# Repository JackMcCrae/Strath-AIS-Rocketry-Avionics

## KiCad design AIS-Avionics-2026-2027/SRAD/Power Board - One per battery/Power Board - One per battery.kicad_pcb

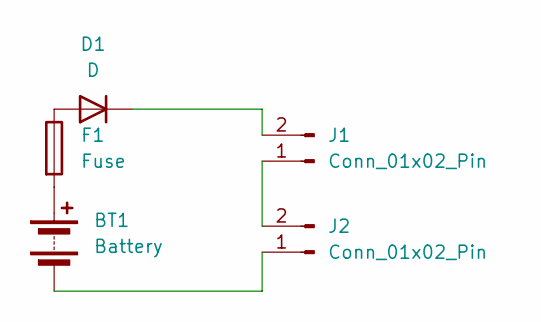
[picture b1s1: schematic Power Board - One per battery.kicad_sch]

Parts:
BT1: Battery; AIS Battery Holder V1
D1: D; TO-264-2_Vertical
F1: Fuse; Fuseholder_Littelfuse_445_030_series_5x30mm
J1, J2: Conn_01x02_Pin; JST_PH_B2B-PH-K_1x02_P2.00mm_Vertical

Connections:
unnamed: BT1.1 (+), F1.2
unnamed: BT1.2 (-), J2.1
unnamed: D1.2 (A), F1.1
unnamed: D1.1 (K), J1.2
unnamed: J1.1, J2.2

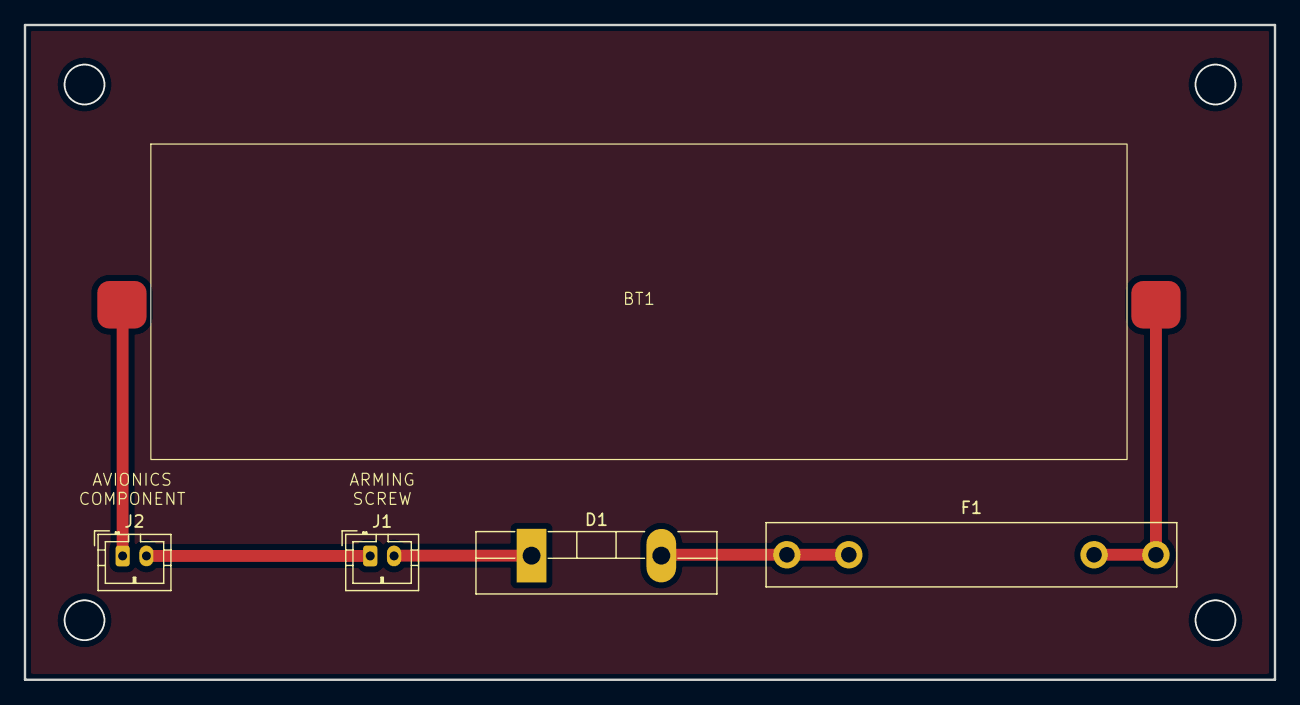
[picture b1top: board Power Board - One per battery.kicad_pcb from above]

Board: 2 copper layers, 105.0 x 55.0 mm, 5 parts (0 on the bottom side), 5 nets.

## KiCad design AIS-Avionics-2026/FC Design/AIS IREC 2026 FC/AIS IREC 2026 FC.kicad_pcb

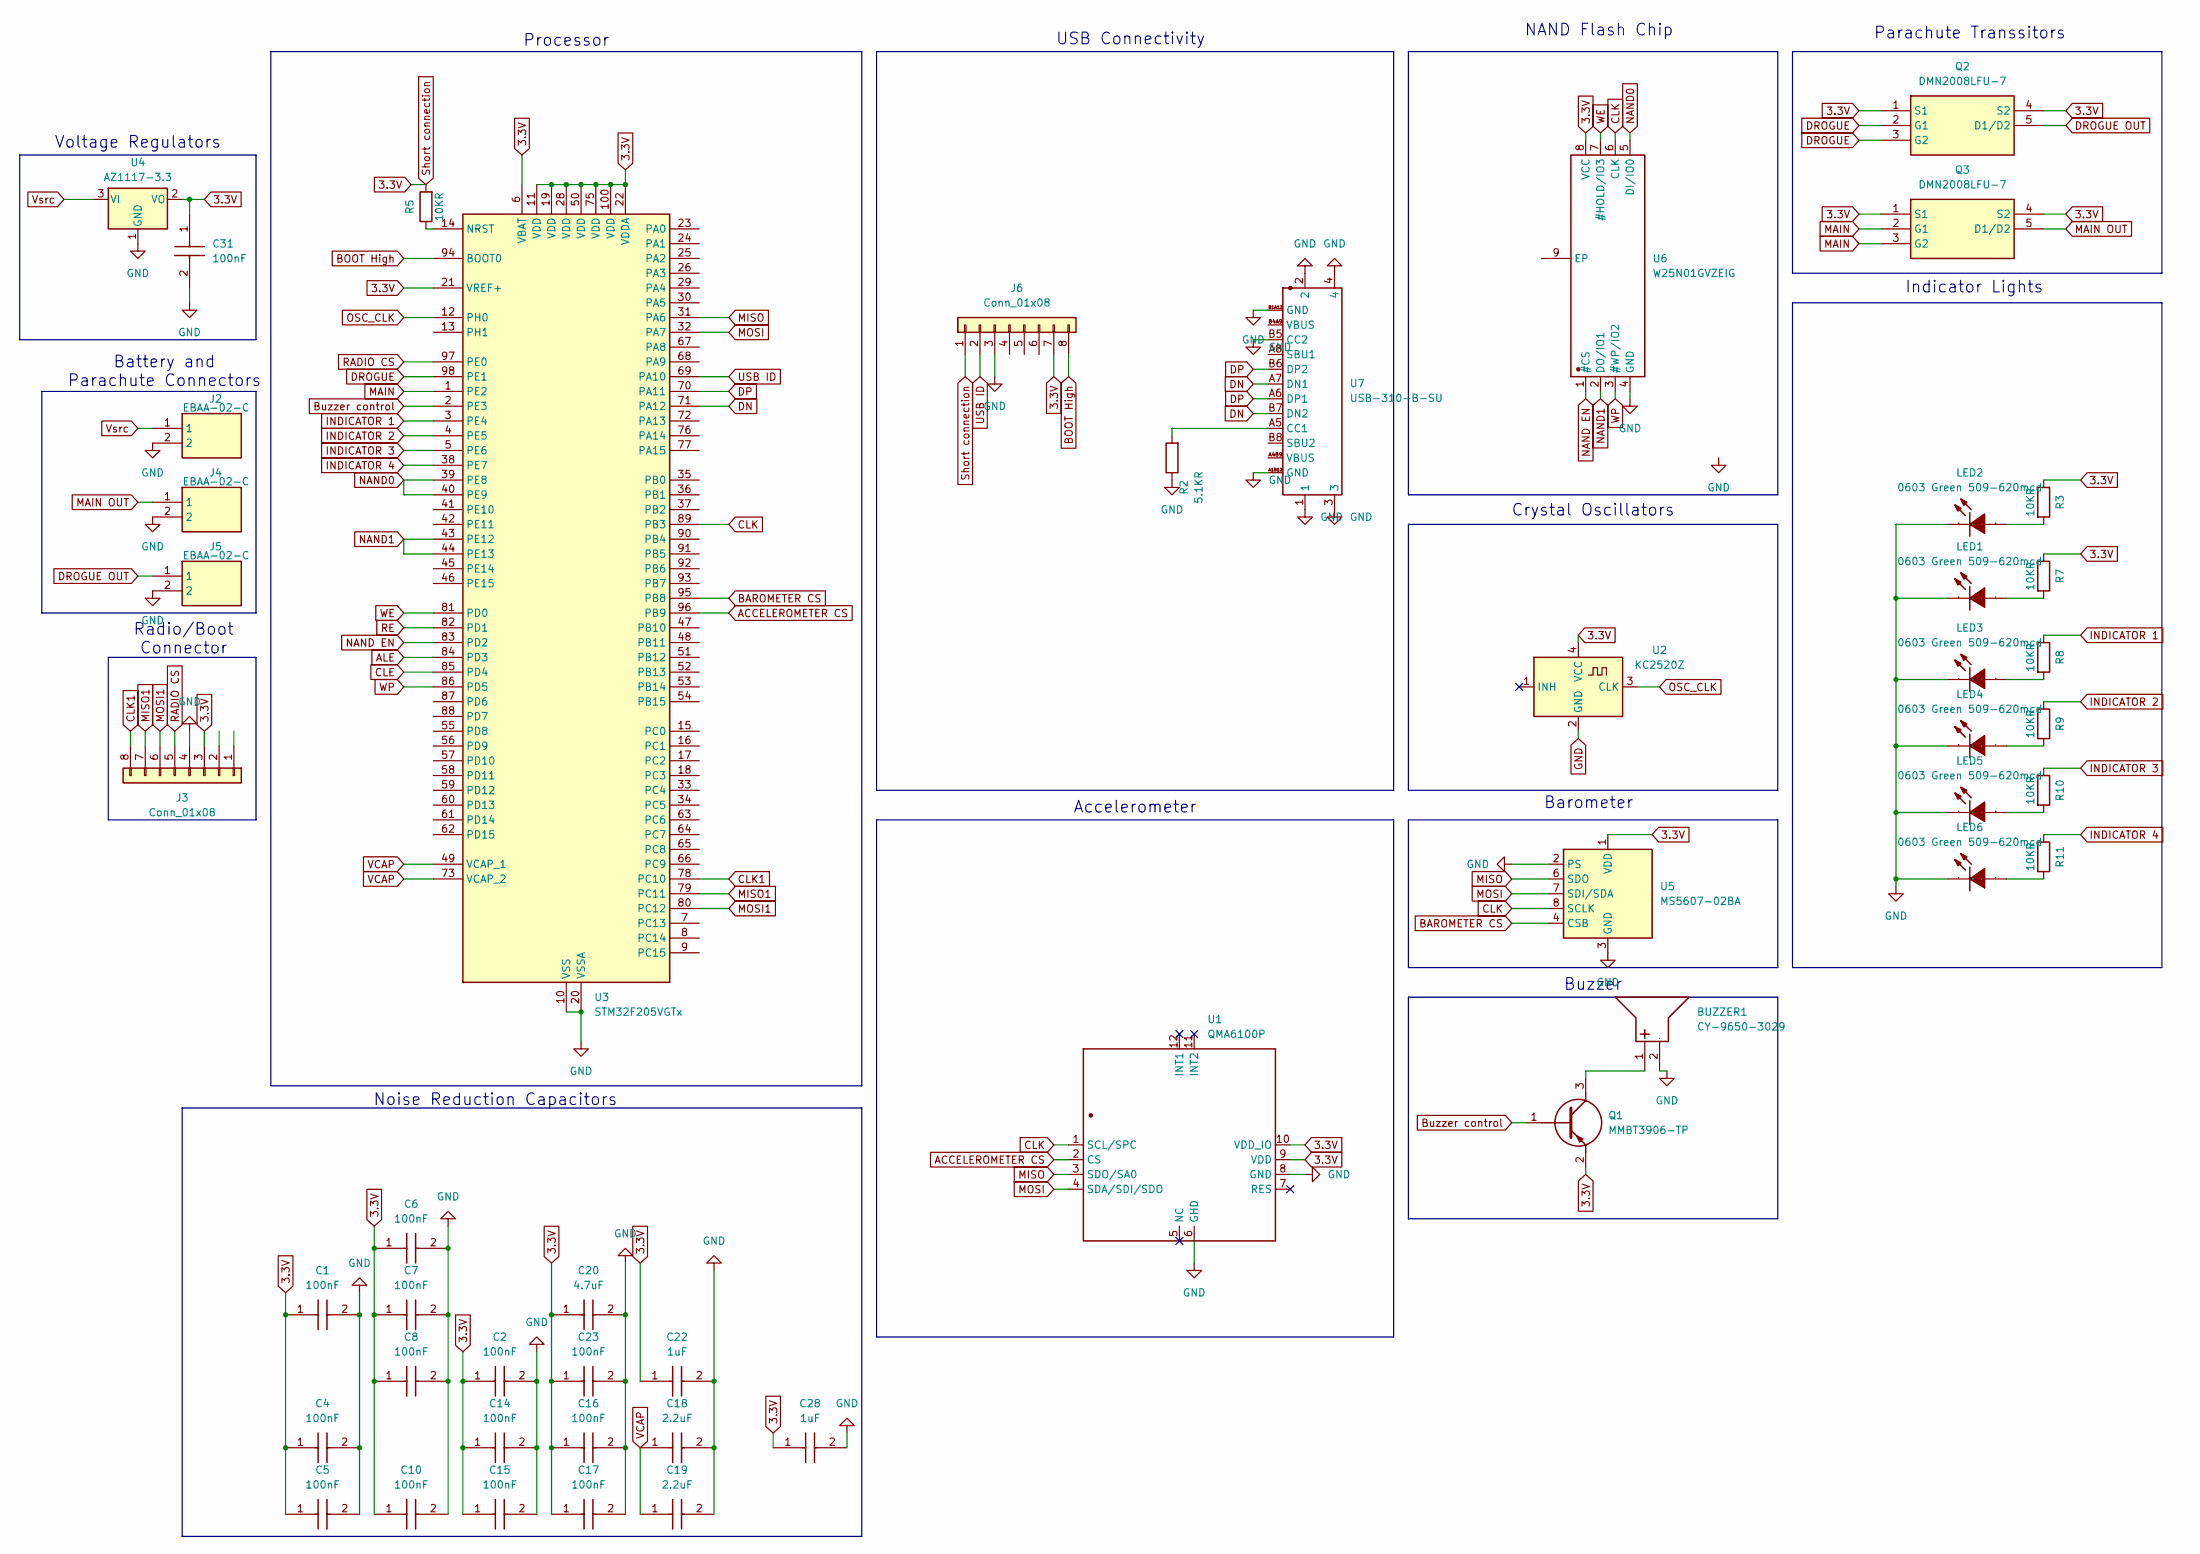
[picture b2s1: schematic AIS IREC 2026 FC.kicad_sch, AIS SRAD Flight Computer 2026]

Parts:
BUZZER1: CY-9650-3029; MLT-9650; Manufacturer Part Cy-9650-3029
C1, C2, C4, C5, C6, C7, C8, C10, C14, C15, C16, C17, C23, C31: 100nF; GRM022C81C222KE01L; Mouser Part Number 81-GRM022R61A104KE1L
C18, C19: 2.2uF; GRM033D70J224ME01D; Mouser Part Number 81-GRM033R61A225KE7D
C20: 4.7uF; GRM033D70J224ME01D; Mouser Part Number 81-GRM035R60J475ME5D
C22, C28: 1uF; CAPC0603X33N; Mouser Part Number 81-GRT033R60J105ME3D
J2, J4, J5: EBAA-02-C; EBAA02C; Mouser Part Number 737-EBAA-02-C
J3, J6: Conn_01x08; Hirose_DF13-08P-1.25DSA_1x08_P1.25mm_Vertical
LED1, LED2, LED3, LED4, LED5, LED6: 0603 Green 509-620mcd; LED0603-RD; Manufacturer Part KT-0603G
Q1: MMBT3906-TP; SOT95P237X125-3N; Mouser Part Number 833-MMBT3906-TP
Q2, Q3: DMN2008LFU-7; DMN2008LFU7; Mouser Part Number 621-DMN2008LFU-7
R2: 5.1KR; R_0201_0603Metric
R3, R5, R7, R8, R9, R10, R11: 10KR; R_0201_0603Metric
U1: QMA6100P; MR ACCELEROMETER; Manufacturer Part QMA6100P
U2: KC2520Z; Oscillator_SMD_Kyocera_KC2520Z-4Pin_2.5x2.0mm
U3: STM32F205VGTx; LQFP-100_14x14mm_P0.5mm
U4: AZ1117-3.3; SOT-223-3_TabPin2
U5: MS5607-02BA; LGA-8_3x5mm_P1.25mm
U6: W25N01GVZEIG; NAND FLASH; Manufacturer Part W25N01GVZEIG
U7: USB-310-B-SU; USB 310F B; Manufacturer Part USB-310-B-SU

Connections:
3.3V: C1.1, C2.1, C4.1, C5.1, C6.1, C7.1, C8.1, C10.1, C14.1, C15.1, C16.1, C17.1, C20.1, C22.1, C23.1, C28.1, C31.1, J3.3, J6.1, J6.7, Q1.2 (E), Q2.1 (S1), Q2.4 (S2), Q3.1 (S1), Q3.4 (S2), R3.1, R5.2, R7.1, U1.9 (VDD), U1.10 (VDD_IO), U2.4 (VCC), U3.6 (VBAT), U3.11 (VDD), U3.19 (VDD), U3.21 (VREF+), U3.22 (VDDA), U3.28 (VDD), U3.50 (VDD), U3.75 (VDD), U3.100 (VDD), U4.2 (VO), U5.1 (VDD), U6.8 (VCC)
ACCELEROMETER CS: U1.2 (CS), U3.96 (PB9)
ALE: U3.84 (PD3)
BAROMETER CS: U3.95 (PB8), U5.4 (CSB), U5.5 (CSB)
BOOT High: J6.8, U3.94 (BOOT0)
Buzzer control: Q1.1 (B), U3.2 (PE3)
CLE: U3.85 (PD4)
CLK: U1.1 (SCL/SPC), U3.89 (PB3), U5.8 (SCLK), U6.6 (CLK)
CLK1: J3.8, U3.78 (PC10)
DN: U3.71 (PA12), U7.A7 (DN1), U7.B7 (DN2)
DP: U3.70 (PA11), U7.A6 (DP1), U7.B6 (DP2)
DROGUE: Q2.2 (G1), Q2.3 (G2), U3.98 (PE1)
DROGUE OUT: J5.1, Q2.5 (D1/D2)
GND: BUZZER1.2 (-), C1.2, C2.2, C4.2, C5.2, C6.2, C7.2, C8.2, C10.2, C14.2, C15.2, C16.2, C17.2, C18.2, C19.2, C20.2, C22.2, C23.2, C28.2, C31.2, J2.2, J3.4, J4.2, J5.2, J6.3, LED1.1 (K), LED2.1 (K), LED3.1 (K), LED4.1 (K), LED5.1 (K), LED6.1 (K), R2.1, U1.6 (GHD), U1.8 (GND), U2.2 (GND), U3.10 (VSS), U3.20 (VSSA), U3.27 (VSS), U3.74 (VSS), U4.1 (GND), U5.2 (PS), U5.3 (GND), U6.4 (GND), U7.1, U7.2, U7.3, U7.4, U7.A1B12 (GND), U7.B1A12 (GND), U7.B5 (CC2)
INDICATOR 1: R8.1, U3.3 (PE4)
INDICATOR 2: R9.1, U3.4 (PE5)
INDICATOR 3: R10.1, U3.5 (PE6)
INDICATOR 4: R11.1, U3.38 (PE7)
MAIN: Q3.2 (G1), Q3.3 (G2), U3.1 (PE2)
MAIN OUT: J4.1, Q3.5 (D1/D2)
MISO: U1.3 (SDO/SA0), U3.31 (PA6), U5.6 (SDO)
MISO1: J3.7, U3.79 (PC11)
MOSI: U1.4 (SDA/SDI/SDO), U3.32 (PA7), U5.7 (SDI/SDA)
MOSI1: J3.6, U3.80 (PC12)
NAND0: U3.39 (PE8), U3.40 (PE9), U6.5 (DI/IO0)
NAND1: U3.43 (PE12), U3.44 (PE13), U6.2 (DO/IO1)
NAND EN: U3.83 (PD2), U6.1 (#CS)
unnamed: BUZZER1.1 (+), Q1.3 (C)
unnamed: LED1.2 (A), R7.2
unnamed: LED2.2 (A), R3.2
unnamed: LED3.2 (A), R8.2
unnamed: LED4.2 (A), R9.2
unnamed: LED5.2 (A), R10.2
unnamed: LED6.2 (A), R11.2
unnamed: R5.1, U3.14 (NRST)
unnamed: R2.2, U7.A5 (CC1)
OSC_CLK: U2.3 (CLK), U3.12 (PH0)
RADIO CS: J3.5, U3.97 (PE0)
RE: U3.82 (PD1)
USB ID: J6.2, U3.69 (PA10)
VCAP: C18.1, C19.1, U3.49 (VCAP_1), U3.73 (VCAP_2)
Vsrc: J2.1, U4.3 (VI)
WE: U3.81 (PD0), U6.7 (#HOLD/IO3)
WP: U3.86 (PD5), U6.3 (#WP/IO2)

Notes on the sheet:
Processor
Indicator Lights
Voltage Regulators
USB Connectivity
Battery and Parachute Connectors
Crystal Oscillators
Barometer
Noise Reduction Capacitors
Radio/Boot Connector
NAND Flash Chip
Buzzer
Accelerometer
Parachute Transsitors

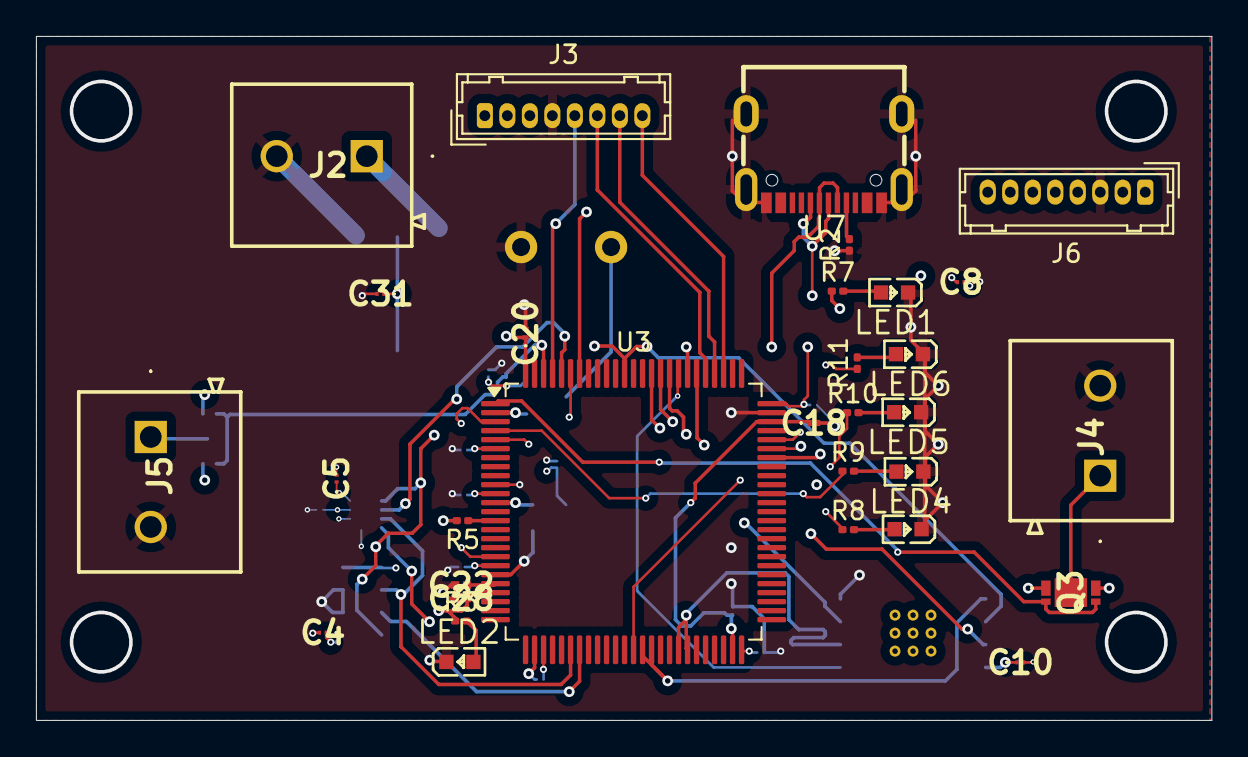
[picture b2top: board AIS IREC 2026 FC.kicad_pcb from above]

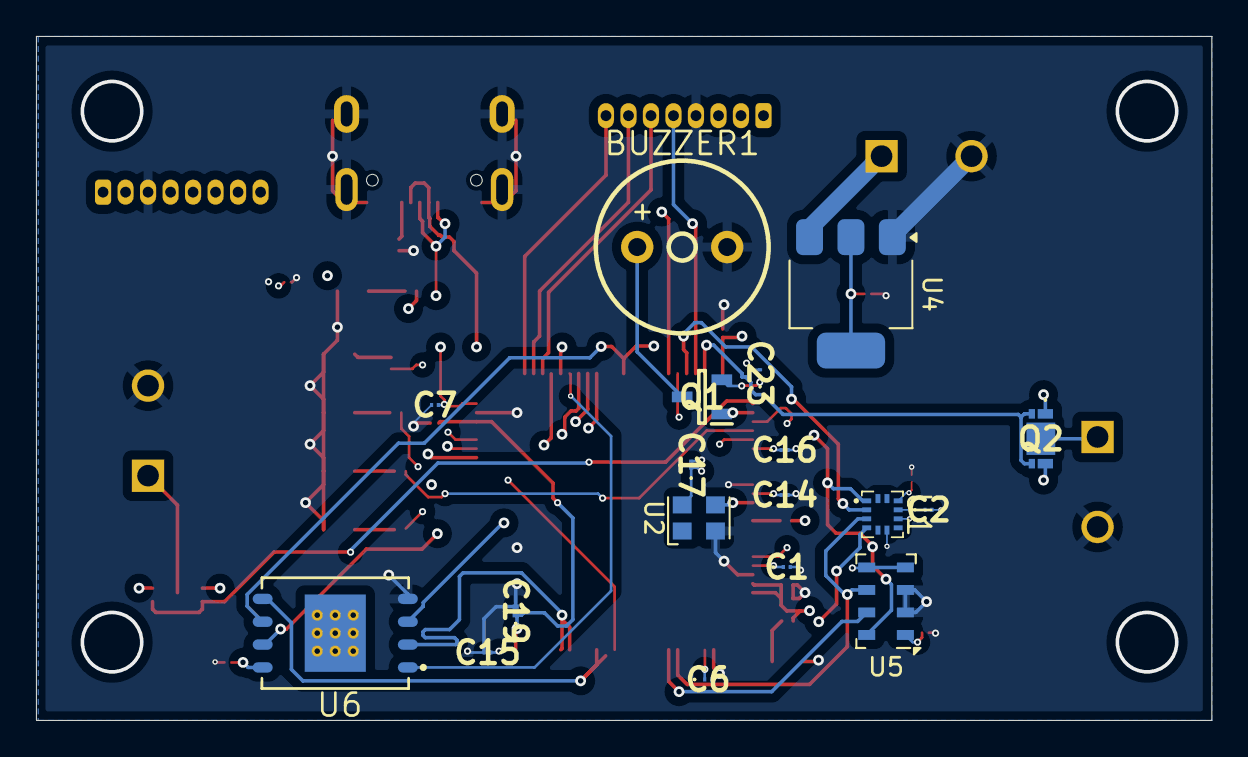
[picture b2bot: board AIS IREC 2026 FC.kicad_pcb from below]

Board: 4 copper layers, 65.3 x 38.0 mm, 49 parts (18 on the bottom side), 41 nets.

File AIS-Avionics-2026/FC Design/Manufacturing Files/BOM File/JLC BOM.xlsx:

Component | Designator | Footprint
CY-9650 | BUZZER1 | MLT-9650
100nF | C1,C2,C4,C5,C6,C7,C8,C10,C14,C15,C16,C17,C23,C31 | GRM022C81C222KE01L
2.2uF | C18,C19 | GRM033D70J224ME01D
4.7uF | C20 | GRM033D70J224ME01D
1uF | C22,C28 | CAPC0603X33N
0603 Green 509-620mcd | LED1,LED2,LED3,LED4,LED5,LED6 | LED0603-RD
10KR | R9,R5,R3,R8,R7,R10,R11 | R_0201_0603Metric
5.1KR | R2 | R_0201_0603Metric
DMN2008LFU-7 | Q3,Q2 | DMN2008LFU7
Conn_01x08 | J6,J3 | Hirose_DF13-08P-1.25DSA_1x08_P1.25mm_Vertical
EBAA-02-C | J5,J4,J2 | EBAA02C
USB-310-B-SU | U7 | UBS-310-B-SU
STM32F205VGT | U3 | STM32F205VGT
MMBT3906-TP | Q1 | SOT95P237X125-3N
KC2520Z | U2 | Oscillator_SMD_Kyocera_KC2520Z-4Pin_2.5x2.0mm
AZ1117-3.3 | U4 | SOT-223-3_TabPin2
MS5607-02BA | U5 | LGA-8_3x5mm_P1.25mm
QMA6100P | U1 | QMA6100P
W25N01GVZEIG | U6 | W25N01GVZEIG

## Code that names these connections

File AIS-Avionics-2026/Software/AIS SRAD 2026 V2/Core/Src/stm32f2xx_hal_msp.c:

/* USER CODE BEGIN Header */
/**
  ******************************************************************************
  * @file         stm32f2xx_hal_msp.c
  * @brief        This file provides code for the MSP Initialization
  *               and de-Initialization codes.
  ******************************************************************************
  * @attention
  *
  * Copyright (c) 2026 STMicroelectronics.
  * All rights reserved.
  *
  * This software is licensed under terms that can be found in the LICENSE file
  * in the root directory of this software component.
  * If no LICENSE file comes with this software, it is provided AS-IS.
  *
  ******************************************************************************
  */
/* USER CODE END Header */

/* Includes ------------------------------------------------------------------*/
#include "main.h"
/* USER CODE BEGIN Includes */

/* USER CODE END Includes */

/* Private typedef -----------------------------------------------------------*/
/* USER CODE BEGIN TD */

/* USER CODE END TD */

/* Private define ------------------------------------------------------------*/
/* USER CODE BEGIN Define */

/* USER CODE END Define */

/* Private macro -------------------------------------------------------------*/
/* USER CODE BEGIN Macro */

/* USER CODE END Macro */

/* Private variables ---------------------------------------------------------*/
/* USER CODE BEGIN PV */

/* USER CODE END PV */

/* Private function prototypes -----------------------------------------------*/
/* USER CODE BEGIN PFP */

/* USER CODE END PFP */

/* External functions --------------------------------------------------------*/
/* USER CODE BEGIN ExternalFunctions */

/* USER CODE END ExternalFunctions */

/* USER CODE BEGIN 0 */

/* USER CODE END 0 */
/**
  * Initializes the Global MSP.
  */
void HAL_MspInit(void)
{

  /* USER CODE BEGIN MspInit 0 */

  /* USER CODE END MspInit 0 */

  __HAL_RCC_SYSCFG_CLK_ENABLE();
  __HAL_RCC_PWR_CLK_ENABLE();

  /* System interrupt init*/

  /* USER CODE BEGIN MspInit 1 */

  /* USER CODE END MspInit 1 */
}

/**
  * @brief SPI MSP Initialization
  * This function configures the hardware resources used in this example
  * @param hspi: SPI handle pointer
  * @retval None
  */
void HAL_SPI_MspInit(SPI_HandleTypeDef* hspi)
{
  GPIO_InitTypeDef GPIO_InitStruct = {0};
  if(hspi->Instance==SPI1)
  {
    /* USER CODE BEGIN SPI1_MspInit 0 */

    /* USER CODE END SPI1_MspInit 0 */
    /* Peripheral clock enable */
    __HAL_RCC_SPI1_CLK_ENABLE();

    __HAL_RCC_GPIOA_CLK_ENABLE();
    __HAL_RCC_GPIOB_CLK_ENABLE();
    /**SPI1 GPIO Configuration
    PA6     ------> SPI1_MISO
    PA7     ------> SPI1_MOSI
    PB3     ------> SPI1_SCK
    */
    GPIO_InitStruct.Pin = GPIO_PIN_6|GPIO_PIN_7;
    GPIO_InitStruct.Mode = GPIO_MODE_AF_PP;
    GPIO_InitStruct.Pull = GPIO_NOPULL;
    GPIO_InitStruct.Speed = GPIO_SPEED_FREQ_VERY_HIGH;
    GPIO_InitStruct.Alternate = GPIO_AF5_SPI1;
    HAL_GPIO_Init(GPIOA, &GPIO_InitStruct);

    GPIO_InitStruct.Pin = GPIO_PIN_3;
    GPIO_InitStruct.Mode = GPIO_MODE_AF_PP;
    GPIO_InitStruct.Pull = GPIO_NOPULL;
    GPIO_InitStruct.Speed = GPIO_SPEED_FREQ_VERY_HIGH;
    GPIO_InitStruct.Alternate = GPIO_AF5_SPI1;
    HAL_GPIO_Init(GPIOB, &GPIO_InitStruct);

    /* USER CODE BEGIN SPI1_MspInit 1 */

    /* USER CODE END SPI1_MspInit 1 */
  }
  else if(hspi->Instance==SPI3)
  {
    /* USER CODE BEGIN SPI3_MspInit 0 */

    /* USER CODE END SPI3_MspInit 0 */
    /* Peripheral clock enable */
    __HAL_RCC_SPI3_CLK_ENABLE();

    __HAL_RCC_GPIOC_CLK_ENABLE();
    /**SPI3 GPIO Configuration
    PC10     ------> SPI3_SCK
    PC11     ------> SPI3_MISO
    PC12     ------> SPI3_MOSI
    */
    GPIO_InitStruct.Pin = GPIO_PIN_10|GPIO_PIN_11|GPIO_PIN_12;
    GPIO_InitStruct.Mode = GPIO_MODE_AF_PP;
    GPIO_InitStruct.Pull = GPIO_NOPULL;
    GPIO_InitStruct.Speed = GPIO_SPEED_FREQ_VERY_HIGH;
    GPIO_InitStruct.Alternate = GPIO_AF6_SPI3;
    HAL_GPIO_Init(GPIOC, &GPIO_InitStruct);

    /* USER CODE BEGIN SPI3_MspInit 1 */

    /* USER CODE END SPI3_MspInit 1 */
  }

}

/**
  * @brief SPI MSP De-Initialization
  * This function freeze the hardware resources used in this example
  * @param hspi: SPI handle pointer
  * @retval None
  */
void HAL_SPI_MspDeInit(SPI_HandleTypeDef* hspi)
{
  if(hspi->Instance==SPI1)
  {
    /* USER CODE BEGIN SPI1_MspDeInit 0 */

    /* USER CODE END SPI1_MspDeInit 0 */
    /* Peripheral clock disable */
    __HAL_RCC_SPI1_CLK_DISABLE();

    /**SPI1 GPIO Configuration
    PA6     ------> SPI1_MISO
    PA7     ------> SPI1_MOSI
    PB3     ------> SPI1_SCK
    */
    HAL_GPIO_DeInit(GPIOA, GPIO_PIN_6|GPIO_PIN_7);

    HAL_GPIO_DeInit(GPIOB, GPIO_PIN_3);

    /* USER CODE BEGIN SPI1_MspDeInit 1 */

    /* USER CODE END SPI1_MspDeInit 1 */
  }
  else if(hspi->Instance==SPI3)
  {
    /* USER CODE BEGIN SPI3_MspDeInit 0 */

    /* USER CODE END SPI3_MspDeInit 0 */
    /* Peripheral clock disable */
    __HAL_RCC_SPI3_CLK_DISABLE();

    /**SPI3 GPIO Configuration
    PC10     ------> SPI3_SCK
    PC11     ------> SPI3_MISO
    PC12     ------> SPI3_MOSI
    */
    HAL_GPIO_DeInit(GPIOC, GPIO_PIN_10|GPIO_PIN_11|GPIO_PIN_12);

    /* USER CODE BEGIN SPI3_MspDeInit 1 */

    /* USER CODE END SPI3_MspDeInit 1 */
  }

}

/* USER CODE BEGIN 1 */

/* USER CODE END 1 */
